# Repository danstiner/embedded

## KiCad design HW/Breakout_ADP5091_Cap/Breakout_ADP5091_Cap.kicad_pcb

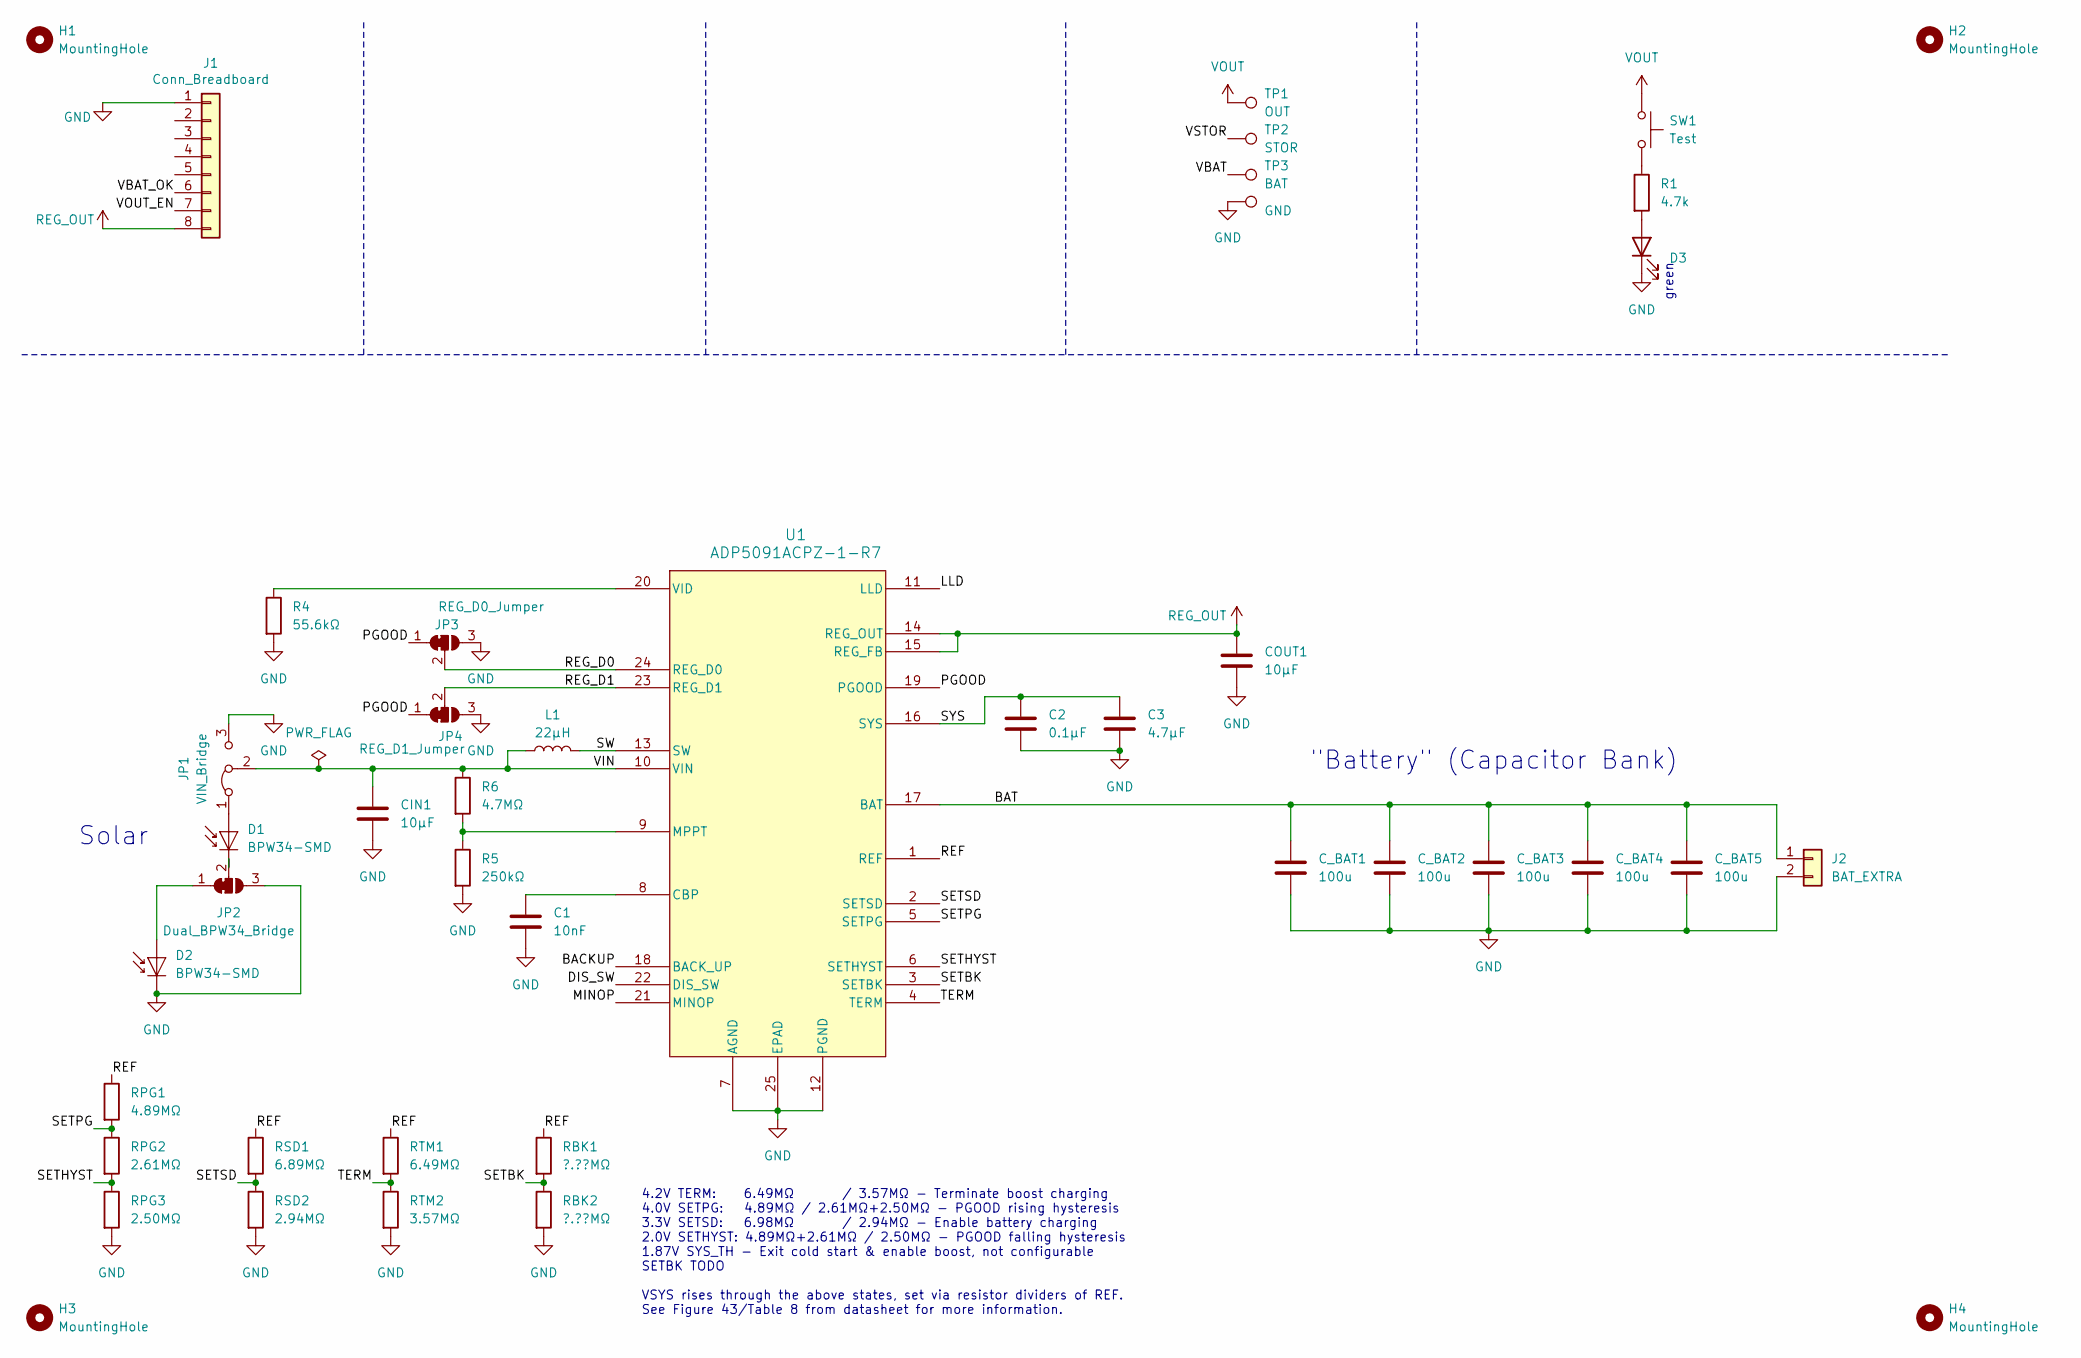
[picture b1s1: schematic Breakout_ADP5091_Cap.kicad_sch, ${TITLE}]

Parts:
C1: 10nF; C_0402_1005Metric
C2: 0.1μF; C_0402_1005Metric
C3: 4.7μF; C_0603_1608Metric
CIN1: 10μF; C_0402_1005Metric
COUT1: 10μF; C_0603_1608Metric
C_BAT1: 100u; C_1206_3216Metric; Digikey Part Number 490-GRM31CR61A107MEA8LCT-ND
C_BAT2, C_BAT3, C_BAT4, C_BAT5: 100u; C_1206_3216Metric
D1, D2: BPW34-SMD; Osram_BPW34S-SMD
D3: PWRLED; LED_0603_1608Metric
H1, H2, H3, H4: MountingHole; MountingHole_2.5mm_Plated
J1: Conn_Breadboard; PinHeader_1x08_P2.54mm_Vertical
J2: BAT_EXTRA; PinHeader_1x02_P2.54mm_Vertical
JP1: VIN_Bridge; PinHeader_1x03_P2.54mm_Vertical
JP2: Dual_BPW34_Bridge; SolderJumper-3_P1.3mm_Bridged12_RoundedPad1.0x1.5mm
JP3: REG_D0_Jumper; SolderJumper-3_P1.3mm_Bridged12_RoundedPad1.0x1.5mm
JP4: REG_D1_Jumper; SolderJumper-3_P1.3mm_Bridged12_RoundedPad1.0x1.5mm
L1: 22μH
R1: 4.7k; R_0603_1608Metric; Digikey Part Number 13-RC0603FR-101KLCT-ND
R4: 55.6kΩ; R_0603_1608Metric
R5: 250kΩ; R_0603_1608Metric
R6: 4.7MΩ; R_0603_1608Metric
RBK1, RBK2: ?.??MΩ; R_0603_1608Metric
RPG1: 4.89MΩ; R_0603_1608Metric
RPG2: 2.61MΩ; R_0603_1608Metric
RPG3: 2.50MΩ; R_0603_1608Metric
RSD1: 6.89MΩ; R_0603_1608Metric
RSD2: 2.94MΩ; R_0603_1608Metric
RTM1: 6.49MΩ; R_0603_1608Metric
RTM2: 3.57MΩ; R_0603_1608Metric
SW1: Test; SW_Push_SPST_NO_Alps_SKRK; Part Number SKRKAHE020; Digikey Part Number 4809-SKRKAHE020CT-ND
TP1: OUT; TestPoint_Pad_D1.0mm
TP2: STOR; TestPoint_Pad_D1.0mm
TP3: BAT; TestPoint_Pad_D1.0mm
TP6: GND; TestPoint_Pad_D1.0mm
U1: ADP5091ACPZ-1-R7; ADP5091ACPZ-1-R7_ADI; Mouser Part Number 771-NEH7100BUHP

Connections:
/BACKUP: U1.18 (BACK_UP)
/BAT: C_BAT1.1, C_BAT2.1, C_BAT3.1, C_BAT4.1, C_BAT5.1, J2.1, U1.17 (BAT)
/DIS_SW: U1.22 (DIS_SW)
/LLD: U1.11 (LLD)
/MINOP: U1.21 (MINOP)
/PGOOD: JP3.1 (A), JP4.1 (A), U1.19 (PGOOD)
/REF: RBK1.1, RPG1.1, RSD1.1, RTM1.1, U1.1 (REF)
/REG_D0: JP3.2 (C), U1.24 (REG_D0)
/REG_D1: JP4.2 (C), U1.23 (REG_D1)
/SETBK: RBK1.2, RBK2.1, U1.3 (SETBK)
/SETHYST: RPG2.2, RPG3.1, U1.6 (SETHYST)
/SETPG: RPG1.2, RPG2.1, U1.5 (SETPG)
/SETSD: RSD1.2, RSD2.1, U1.2 (SETSD)
/SW: L1.2, U1.13 (SW)
/SYS: C2.1, C3.1, U1.16 (SYS)
/TERM: RTM1.2, RTM2.1, U1.4 (TERM)
/VBAT: TP3.1
/VBAT_OK: J1.6
/VIN: CIN1.1, JP1.2 (C), L1.1, R6.1, U1.10 (VIN)
/VOUT_EN: J1.7
/VSTOR: TP2.1
GND: C1.2, C2.2, C3.2, CIN1.2, COUT1.2, C_BAT1.2, C_BAT2.2, C_BAT3.2, C_BAT4.2, C_BAT5.2, D2.1 (K), D3.1 (K), J1.1, J2.2, JP1.3 (B), JP2.3 (B), JP3.3 (B), JP4.3 (B), R4.2, R5.2, RBK2.2, RPG3.2, RSD2.2, RTM2.2, TP6.1, U1.7 (AGND), U1.12 (PGND), U1.25 (EPAD)
unnamed: D1.2 (A), JP1.1 (A)
unnamed: D1.1 (K), JP2.2 (C)
unnamed: D2.2 (A), JP2.1 (A)
unnamed: D3.2 (A), R1.2
unnamed: R1.1, SW1.2
unnamed: C1.1, U1.8 (CBP)
unnamed: R5.1, R6.2, U1.9 (MPPT)
unnamed: R4.1, U1.20 (VID)
REG_OUT: COUT1.1, J1.8, U1.14 (REG_OUT), U1.15 (REG_FB)
VOUT: SW1.1, TP1.1

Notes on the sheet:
Solar
4.2V TERM: 6.49MΩ / 3.57MΩ - Terminate boost charging 4.0V SETPG: 4.89MΩ / 2.61MΩ+2.50MΩ - PGOOD rising hysteresis 3.3V SETSD: 6.98MΩ / 2.94MΩ - Enable battery charging 2.0V SETHYST: 4.89MΩ+2.61MΩ / 2.50MΩ - PGOOD falling hysteresis 1.87V SYS_TH - Exit cold start & enable boost, not configurable SE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
green
"Battery" (Capacitor Bank)

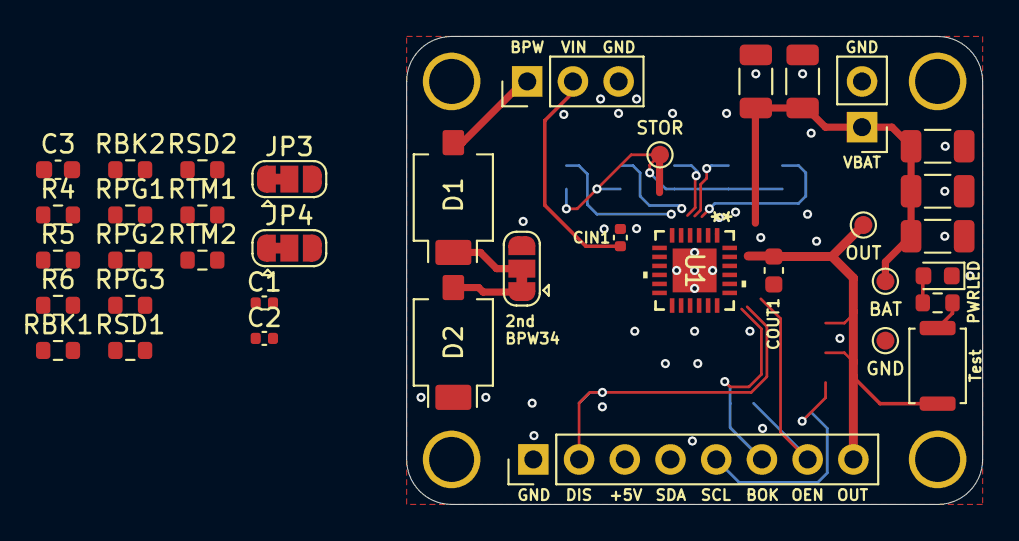
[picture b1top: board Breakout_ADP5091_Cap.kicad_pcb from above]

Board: 2 copper layers, 32.0 x 26.0 mm, 42 parts (0 on the bottom side), 23 nets.
